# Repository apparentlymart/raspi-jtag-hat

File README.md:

# Raspberry Pi 3 Bare Metal Dev HAT

This repository contains KiCad design files for an **experimental** Raspberry
Pi "pseudo-HAT" (lacking an ID EEPROM) that breaks out the JTAG and UART pins
to an ARM-style JTAG header and a 6-pin "FTDI header" respectively. The goal
is to make it easy to connect diagnostic tools from a host development machine
when working on bare-metal software for the Raspberry Pi 3.

The author makes no promises or warranty about the quality or functionality of
this PCB design. Your mileage may vary. However, if you would like to give it a
try, either clone the repo and load the project into KiCad or download the
Gerber files attached to one of the
[tagged revisions](https://github.com/apparentlymart/raspi-jtag-hat/releases).
Before spending any time and money, please consider checking for any
[open issues](https://github.com/apparentlymart/raspi-jtag-hat/issues), and
for any _closed_ issues that apply to the tagged revision you are working with.

The board also includes extra breakouts for the I2C pins and the power pins
from the main header, as an optional convenience. It might also work for
Raspberry Pi 2, but its unusual L-shape is intended to avoid conflicts with
the larger heatsinks that some owners fit to their Raspberry Pi 3 units.

The following is an example BOM for some through-hole components that could
be used to populate this PCB:

| Ref. | Description                     | Octopart Id                                                                                               |
| ---- | ------------------------------- | --------------------------------------------------------------------------------------------------------- |
| P1   | "FTDI-style" UART header        | [22-28-4063-molex-278209](https://octopart.com/22-28-4063-molex-278209)                                   |
| P2   | Raspberry Pi Main header socket | [hif3h-40da-2.54dsa(71)-hirose-22821340](https://octopart.com/hif3h-40da-2.54dsa%2871%29-hirose-22821340) |
| P3   | "ARM-style" JTAG socket         | [htst-110-01-l-d-samtec-6823793](https://octopart.com/htst-110-01-l-d-samtec-6823793)                     |
| P4   | Misc. Power header              | [10-89-7082-molex-20831](https://octopart.com/10-89-7082-molex-20831)                                     |
| P5   | I2C header                      | [10-89-7042-molex-35512](https://octopart.com/10-89-7042-molex-35512)                                     |
| n/a  | Board Spacer (optional)         | [mdlsp3-6-01-essentra-33826524](https://octopart.com/mdlsp3-6-01-essentra-33826524)                       |

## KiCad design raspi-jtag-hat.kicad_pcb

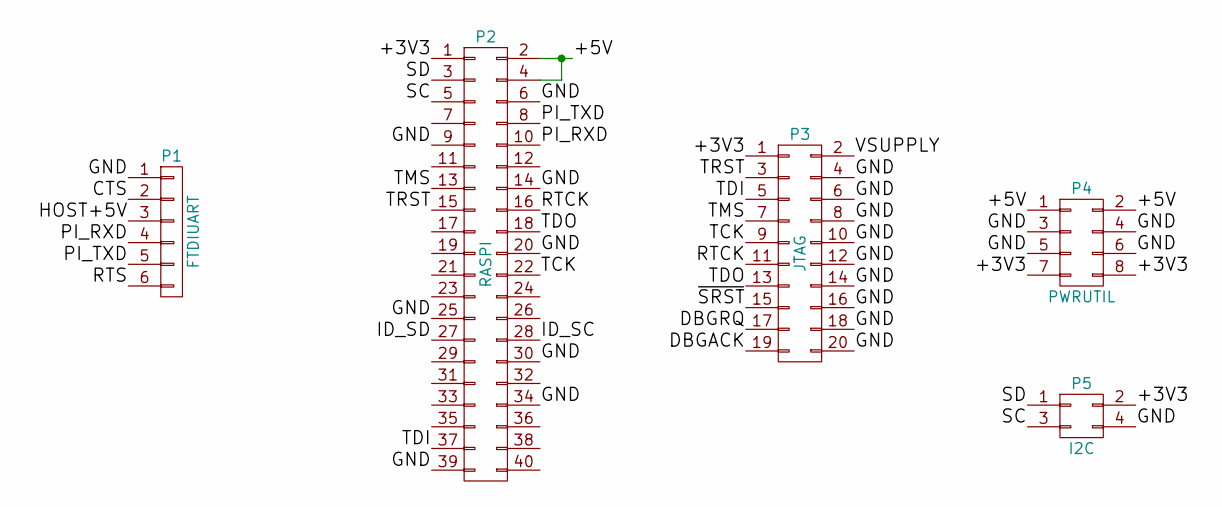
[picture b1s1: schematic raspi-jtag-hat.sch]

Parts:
P1: FTDIUART
P2: RASPI
P3: JTAG
P4: PWRUTIL
P5: I2C

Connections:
/+3V3: P2.1, P3.1, P4.7, P4.8, P5.2
/+5V: P2.2, P2.4, P4.1, P4.2
/CTS: P1.2
/DBGACK: P3.19
/DBGRQ: P3.17
/GND: P1.1, P2.6, P2.9, P2.14, P2.20, P2.25, P2.30, P2.34, P2.39, P3.4, P3.6, P3.8, P3.10, P3.12, P3.14, P3.16, P3.18, P3.20, P4.3, P4.4, P4.5, P4.6, P5.4
/HOST+5V: P1.3
/ID_SC: P2.28
/ID_SD: P2.27
/PI_RXD: P1.4, P2.10
/PI_TXD: P1.5, P2.8
/RTCK: P2.16, P3.11
/RTS: P1.6
/SC: P2.5, P5.3
/SD: P2.3, P5.1
/TCK: P2.22, P3.9
/TDI: P2.37, P3.5
/TDO: P2.18, P3.13
/TMS: P2.13, P3.7
/TRST: P2.15, P3.3
/VSUPPLY: P3.2
/~SRST: P3.15

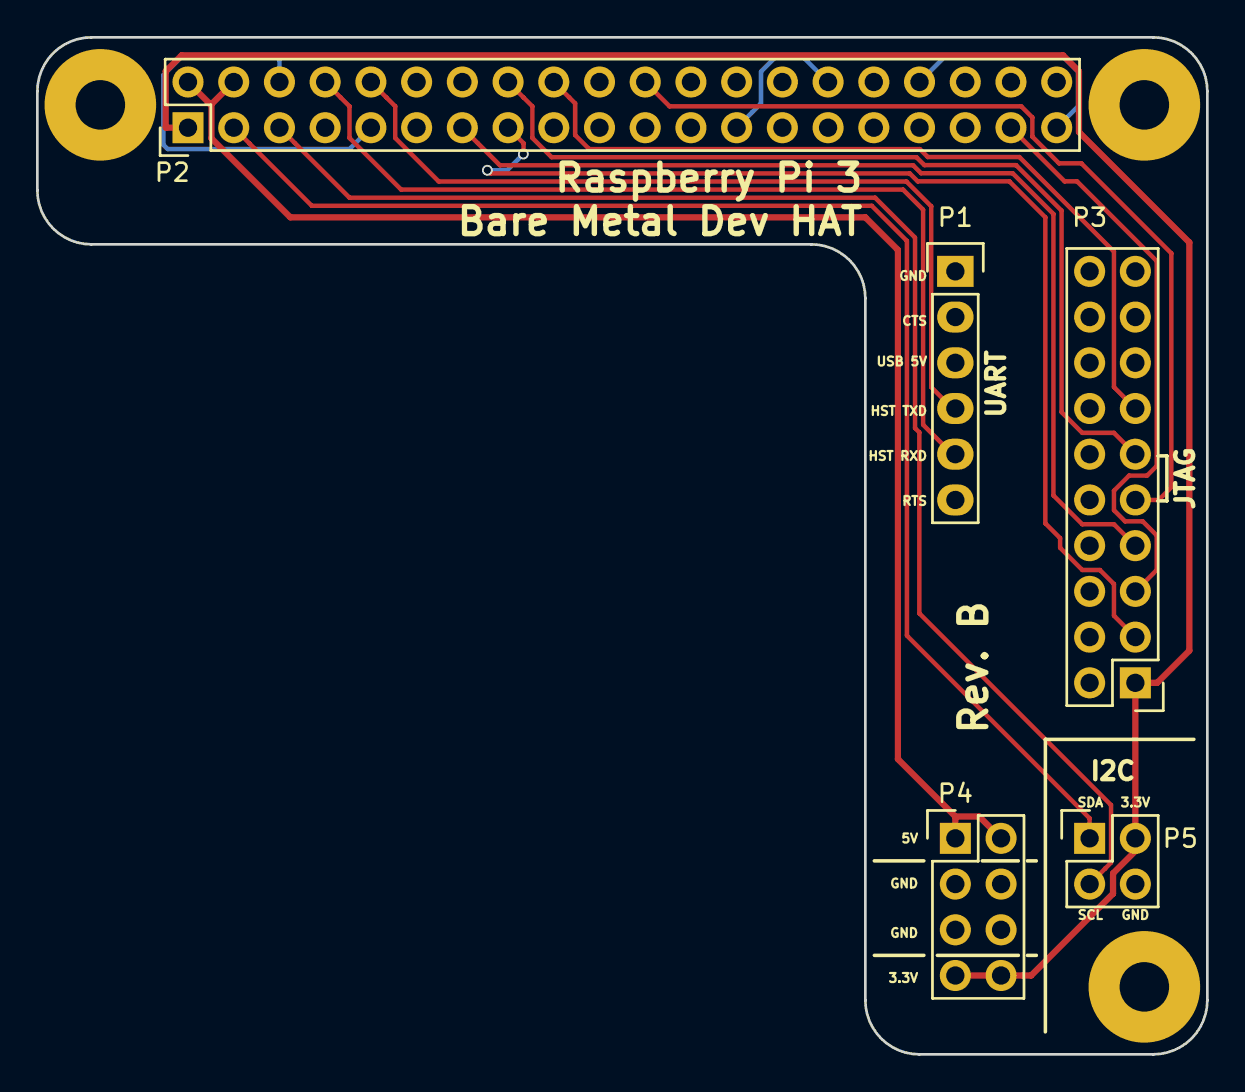
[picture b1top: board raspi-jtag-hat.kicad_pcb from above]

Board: 2 copper layers, 65.0 x 56.5 mm, 5 parts (0 on the bottom side), 13 nets.

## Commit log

2018-07-28 Initial import
2018-07-28 Add LICENSE (CC-BY-3.0)
2018-07-28 Initial README
2018-07-28 Complete the BOM in the README
2018-07-28 Add an example optional board spacer to the BOM
2018-07-28 Warn in README about open issues
    Although there's no warranty at all on this thing, I'd still prefer that
    people don't stumble across this and spend money on it only to encounter
    a known design problem.
2018-07-29 Add a small kernel that just enables JTAG and halts all CPU cores
    This is handy to quickly get the Pi up and running with the JTAG pin ALT
    functions enabled so the real work of loading the target program can be
    done over JTAG with OpenOCD/gdb.
2018-07-29 Schematic library cache file
    I just missed this on the first round of commits.
2018-07-29 Makefile for automating a "release" of the stuff in here
    This uses the KiCad pcbnew Python interface to render Gerber files, builds
    the boot filesystem files, and then produces two zip files that can be
    attached to a published release for a new revision.
2018-07-29 Generate a preview image with gerbv when preparing dist
2018-07-29 Change 3.3V header silkscreen caption to "3.3V"
    Previously it said just "3V".
2018-07-29 Update board silkscreen in preparation for Rev. B.
2018-07-29 Suppress edge lines on other layers when generating Gerber files
